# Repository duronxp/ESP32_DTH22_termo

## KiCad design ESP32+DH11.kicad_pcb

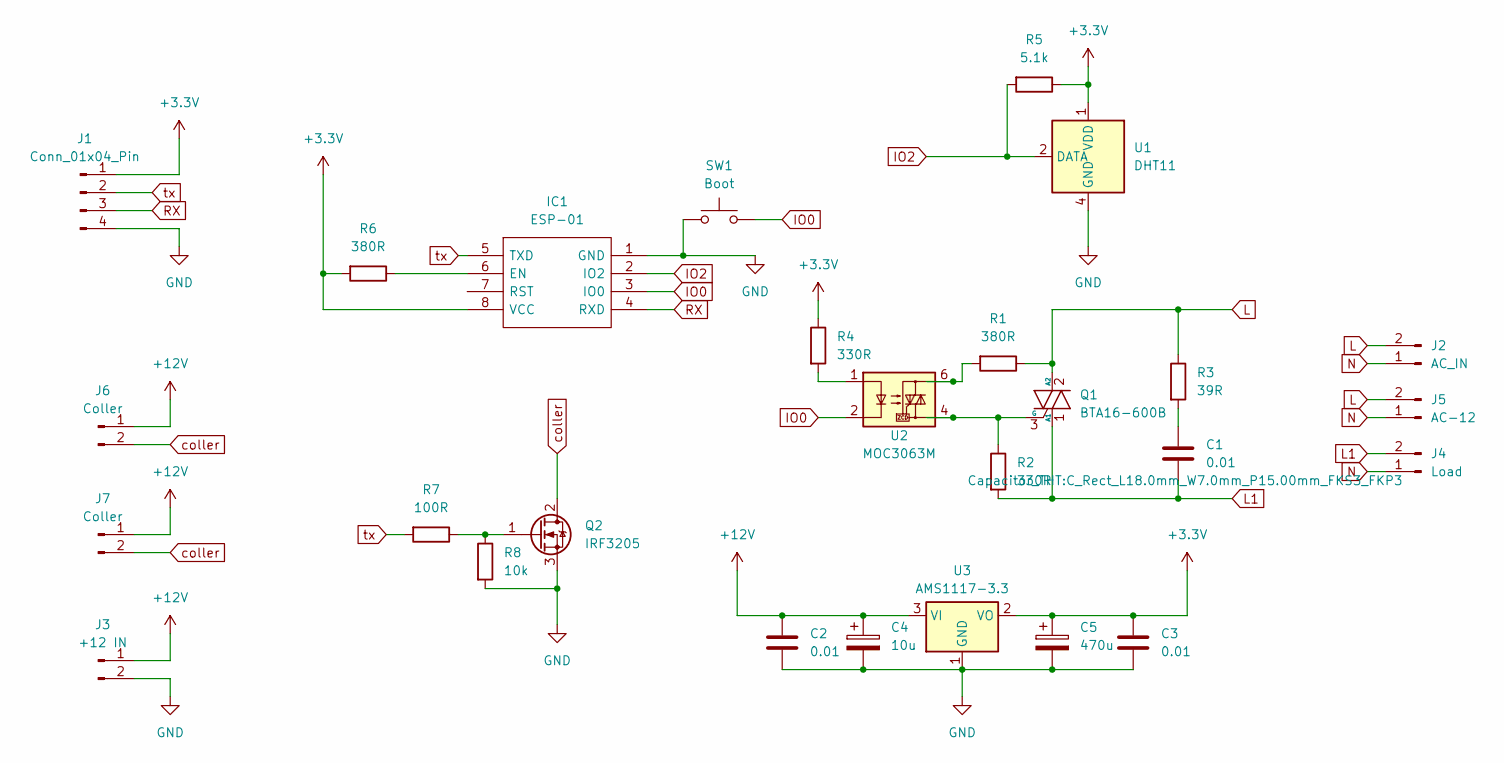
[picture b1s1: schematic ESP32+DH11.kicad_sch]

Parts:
C1: 0.01; C_Rect_L18.0mm_W7.0mm_P15.00mm_FKS3_FKP3
C2, C3: 0.01; C_1206_3216Metric_Pad1.33x1.80mm_HandSolder
C4: 10u; CP_Elec_6.3x7.7
C5: 470u; CP_Elec_6.3x7.7
IC1: ESP-01; Manufacturer_Part_Number ESP-01
J1: Conn_01x04_Pin; PinHeader_1x04_P2.54mm_Vertical
J2: AC_IN; JWT_A3963_1x02_P3.96mm_Vertical
J3: +12 IN; JST_XH_B2B-XH-AM_1x02_P2.50mm_Vertical
J4: Load; JWT_A3963_1x02_P3.96mm_Vertical
J5: AC-12; JWT_A3963_1x02_P3.96mm_Vertical
J6, J7: Coller; JST_XH_B2B-XH-AM_1x02_P2.50mm_Vertical
Q1: BTA16-600B; TO-220-3_Vertical
Q2: IRF3205; TO-220-3_Vertical
R1: 380R; R_Axial_DIN0207_L6.3mm_D2.5mm_P10.16mm_Horizontal
R2: 330R; R_Axial_DIN0207_L6.3mm_D2.5mm_P10.16mm_Horizontal
R3: 39R; R_Axial_DIN0207_L6.3mm_D2.5mm_P10.16mm_Horizontal
R4: 330R; R_1210_3225Metric_Pad1.30x2.65mm_HandSolder
R5: 5.1k; R_1206_3216Metric_Pad1.30x1.75mm_HandSolder
R6: 380R; R_1206_3216Metric_Pad1.30x1.75mm_HandSolder
R7: 100R; R_1206_3216Metric_Pad1.30x1.75mm_HandSolder
R8: 10k; R_1206_3216Metric_Pad1.30x1.75mm_HandSolder
SW1: Boot; SW_SPST_TL3305A
U1: DHT11; Aosong_DHT11_5.5x12.0_P2.54mm
U2: MOC3063M; DIP-6_W7.62mm
U3: AMS1117-3.3; SOT-89-3_Handsoldering

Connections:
+3.3V: C3.1, C5.1, IC1.8 (VCC), J1.1, R4.1, R5.1, R6.2, U1.1 (VDD), U3.2 (VO)
+12V: C2.1, C4.1, J3.1, J6.1, J7.1, U3.3 (VI)
GND: C2.2, C3.2, C4.2, C5.2, IC1.1 (GND), J1.4, J3.2, Q2.3 (S), R8.2, SW1.1, U1.4 (GND), U3.1 (GND)
IO0: IC1.3 (IO0), SW1.2, U2.2
IO2: IC1.2 (IO2), R5.2, U1.2 (DATA)
L: J2.2, J5.2, Q1.2 (A2), R1.1, R3.1
L1: C1.2, J4.2, Q1.1 (A1), R2.2
N: J2.1, J4.1, J5.1
unnamed: C1.1, R3.2
unnamed: IC1.6 (EN), R6.1
unnamed: Q1.3 (G), R2.1, U2.4
unnamed: Q2.1 (G), R7.1, R8.1
unnamed: R1.2, U2.6
unnamed: R4.2, U2.1
RX: IC1.4 (RXD), J1.3
coller: J6.2, J7.2, Q2.2 (D)
tx: IC1.5 (TXD), J1.2, R7.2

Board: 2 copper layers, 27 parts (0 on the bottom side), 17 nets, no tracks yet.

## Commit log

2024-12-28 init commit
